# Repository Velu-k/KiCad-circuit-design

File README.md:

# 555 timer
Electrical schematics and layout has designed in KiCad software using SMD[Surface Mount Device] and THT[Thorough Hole Technology].
This project demonstrates the use of a 555 timer in SMD format to generate precise timing pulses for LED blinking, frequency generation, and pulse-width modulation applications.”

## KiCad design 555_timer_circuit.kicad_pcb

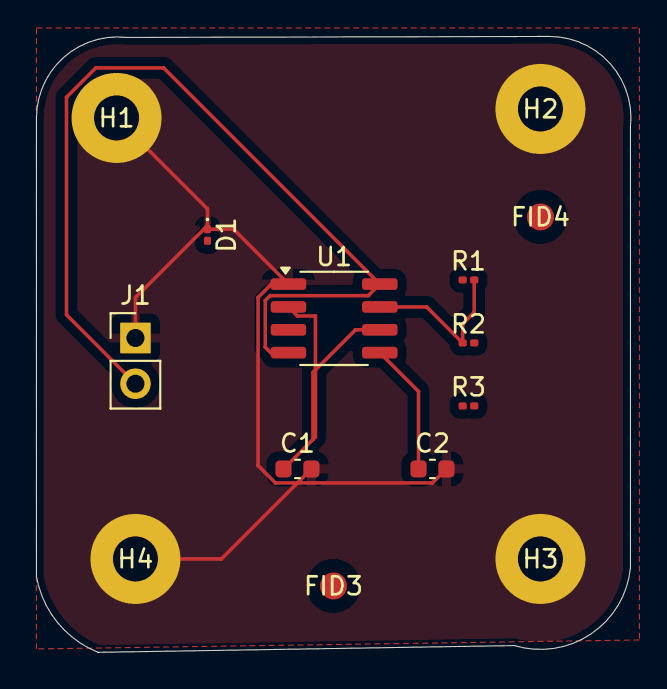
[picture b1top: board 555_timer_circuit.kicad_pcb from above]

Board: 2 copper layers, 33.0 x 34.2 mm, 14 parts (0 on the bottom side), 7 nets.

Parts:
C1, C2: 0.1 uF; C_0603_1608Metric
D1: LED; LED_0201_0603Metric
FID3, FID4: Fiducial; Fiducial_1.5mm_Mask3mm
H1, H2, H3, H4: MH; MountingHole_2.5mm_Pad
J1: Power Input; PinHeader_1x02_P2.54mm_Vertical
R1, R2: 10k; R_0201_0603Metric
R3: 1k; R_0201_0603Metric
U1: ICM7555xB; SOP-8_3.76x4.96mm_P1.27mm

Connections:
DIS: R1.2, R2.1, U1.7 (DIS)
GND: C1.2, C2.2, D1.1 (K), H1.1, H2.1, H3.1, H4.1, J1.1, U1.1 (GND)
unnamed: D1.2 (A), R3.2
unnamed: C2.1, U1.5 (CV)
unnamed: R3.1, U1.3 (Q)
TRG: C1.1, R2.2, U1.2 (TR), U1.6 (THR)
vcc: J1.2, R1.1, U1.4 (R), U1.8 (VCC)
